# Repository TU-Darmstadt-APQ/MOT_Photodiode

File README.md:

# MOT Photodiode
This is a photodiode board with a transimpedance amplifier for [S-100](https://osioptoelectronics.com/media/pages/products/photodetectors/solderable-chip-photodiodes/s-100vl/1aa00dfa44-1675100439/solderable-chips.pdf) photodiodes used to probe the MOT beams at the QUIPS-C experiment.
The photodiode is inserted into the laser beam on a slide-in unit ([slide_in_mount](photodiode_mount/slide_in_mount.ipt) in combination with the [photo_plate_slide_in](photodiode_mount/photo_plate_slide_in.ipt)) which can be placed behind the MOT Beam Doublett collimators. This assembly is mounted on a flange screwed to the vacuum chamber (viewport_mount assembly designed by Lars Pause). The photodiode board can be screwed on this holder with two polymer screws. 

## Contents
- [Introduction](#introduction)
- [Design files](#design-files)
- [Related repositories](#related-repositories)
- [Versioning](#versioning)
- [License](#license)

## Introduction
The photodiode board features a single-stage amplifier and a voltage regulator to power the op-amp. The power supply required needs to provide +-15 V via a pin header. The bandwidth of the system is about 10 kHz. For details see [here](datasheet/bandwidth.png).

## Design files
### For production
The design files required for the PCB production and assembly can be found on the [releases](../../releases) page and include the following resources:

- Schematics as a PDF
- Gerber files
- Pick & place position files
- Bill of materials as a CSV file and also as an interactive HTML version
- Mechanical design files for manufacturing the housing as PDF

The latest revision of those files can be found [here](../../releases/latest).

### For editing
To work on the [KiCad](https://www.kicad.org/) design files, a number of external libraries are needed. Those libraries show up as empty folders in the zip file, because they are not included in the release, but must be downloaded separately from the links given [below](#related-repositories). This can be avoided by checking out the whole repository using git. This way the libraries will be downloaded as well. Use the following command to clone the git repository along with the submodules  using the `--recurse-submodules` flag.
```
git clone --recurse-submodules https://github.com/TU-Darmstadt-APQ/MOT_Photodiode.git
```

## Related repositories
See the following repositories for more information as these are part of the [design files](#design Files).

- [KiCad footprints](https://github.com/PatrickBaus/footprints.pretty)
- [KiCAD 3D models](https://github.com/PatrickBaus/footprints.3dshapes)
- [KiCAD schematic libraries](https://github.com/PatrickBaus/KiCad-libraries)

## Versioning
I use [SemVer](http://semver.org/) for versioning. For the versions available, see the [tags](../../tags) available for this repository.

- MAJOR versions in this context mean a breaking change to the external interface of the hardware like different connectors or functions.
- MINOR versions contain changes to the hardware that only affect the inner workings of the circuit, but otherwise the performance is unaffected.
- PATCH versions do not affect the schematics or invalidate older bill of materials. These changes may include updated components (to replace obsolete parts for example), an updated silkscreen, or fixed typos.

## License
This work is released under the CERN-OHL-W
See [https://ohwr.org/cern_ohl_w_v2.pdf](https://ohwr.org/cern_ohl_w_v2.pdf) or the included [LICENSE](LICENSE) file for more information.

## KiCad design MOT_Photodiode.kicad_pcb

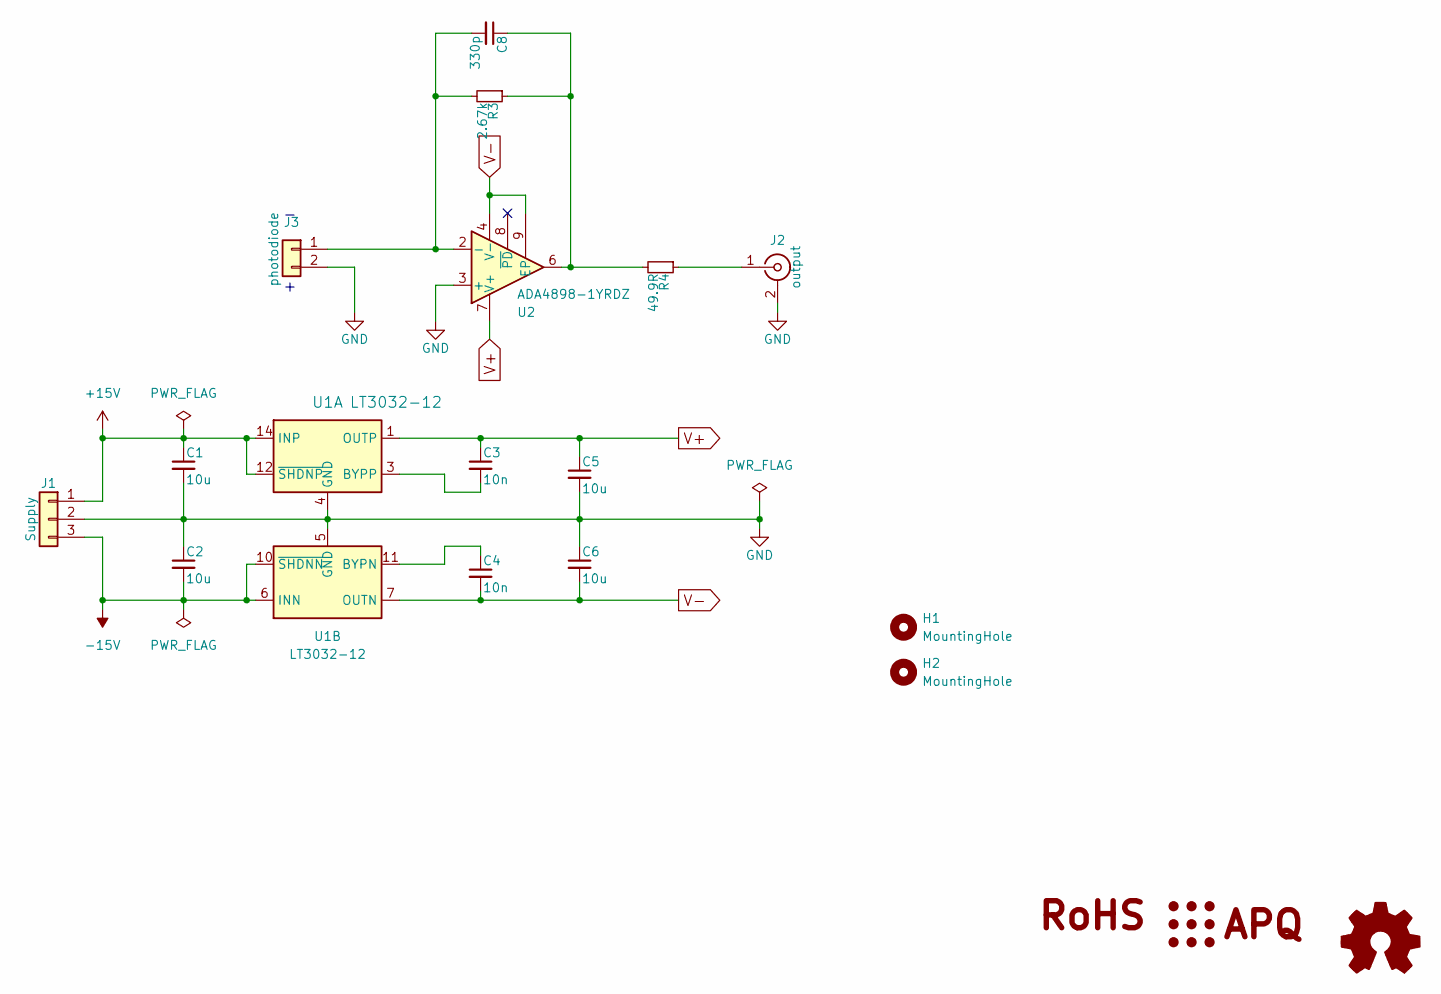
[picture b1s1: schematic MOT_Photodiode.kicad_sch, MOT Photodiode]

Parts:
C1, C2, C5, C6: 10u; C_1210_3225Metric
C3, C4: 10n; C_0603_1608Metric
C8: 330p; C_0603_1608Metric
H1, H2: MountingHole; MountingHole_3.2mm_M3
J1: Supply; PinHeader_1x03_P2.54mm_Vertical
J2: output; SMA_Amphenol_132134_Vertical
J3: photodiode; PinHeader_1x02_P2.54mm_Vertical
R3: 2.67k; R_0603_1608Metric
R4: 49.9R; R_1210_3225Metric
SYM1: Logo_Open_Hardware_Small; OSHW-Logo_7.5x8mm_SilkScreen
SYM2: Logo_APQ; APQ-Logo_small
U1: LT3032-12; Linear_DE14MA
U2: ADA4898-1YRDZ; SOIC-8-1EP_3.9x4.9mm_P1.27mm_EP2.29x3mm

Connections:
+15V: C1.1, J1.1, U1.12 (~SHDNP), U1.14 (INP)
-15V: C2.2, J1.3, U1.6 (INN), U1.9 (INN), U1.10 (~SHDNN)
GND: C1.2, C2.1, C5.2, C6.1, J1.2, J2.2 (Ext), J3.2, U1.4 (GND), U1.5 (GND), U2.3 (+)
unnamed: C8.1, R3.1, R4.2, U2.6
unnamed: J2.1 (In), R4.1
unnamed: C8.2, J3.1, R3.2, U2.2 (-)
unnamed: C3.2, U1.3 (BYPP)
unnamed: C4.1, U1.11 (BYPN)
V+: C3.1, C5.1, U1.1 (OUTP), U2.7 (V+)
V-: C4.2, C6.2, U1.7 (OUTN), U2.4 (V-), U2.9 (EP)

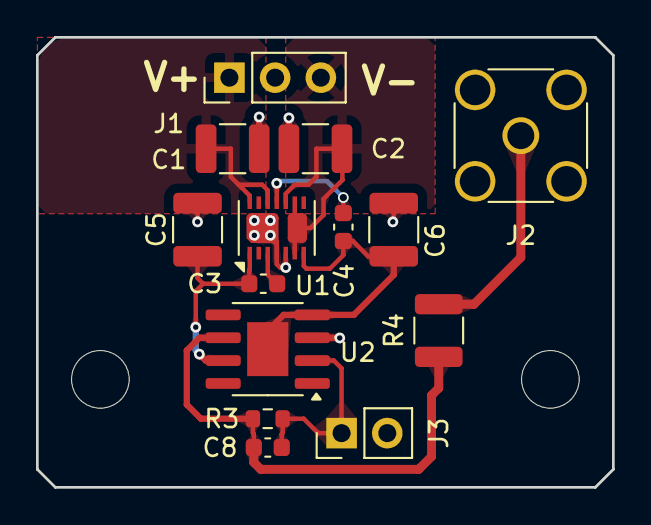
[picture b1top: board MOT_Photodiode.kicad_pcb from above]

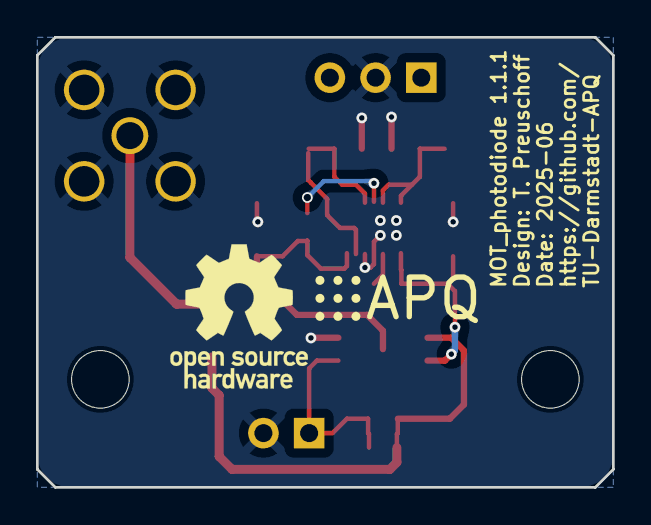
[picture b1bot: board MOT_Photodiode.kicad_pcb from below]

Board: 2 copper layers, 32.0 x 25.0 mm, 18 parts (2 on the bottom side), 10 nets.

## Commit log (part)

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2025-02-27 Cleanup
2025-02-27 Added logos
2025-02-27 Chamfered corners
2025-02-27 Reduced via drill size from 0.4 mm to 0.3 mm
2025-02-27 Added teardrops
2025-02-27 Added BOM
2025-02-27 Added readme
2025-02-27 Added license
2025-02-28 add description
2025-02-28 add comment for to versioning
2025-03-07 add ipt inventor Files
    Original files and whole assembly of viewport_mount can be found on Brain:
    Labortechnik\Mechanik\QUIPS_C\Vakuumkammer_assembly\viewport_flanges
2025-06-24 Update files to KiCad 9
2025-06-24 Bump CI to KiCad 9
2025-06-24 Refilled copper pour
2025-06-24 Bump version to 1.1.1
2025-06-24 More version bumping to 1.1.1
2025-06-24 Update/kicad9 (#2)
    * Update files to KiCad 9 incl. footprint updates
    * Bump CI to KiCad 9
    * Refilled copper pour
    * Bump version to 1.1.1
2025-06-24 Updated readme and added mechanical design files (#1)
    * add description
    * add ipt inventor Files
    Original files and whole assembly of viewport_mount can be found on Brain:
    Labortechnik\Mechanik\QUIPS_C\Vakuumkammer_assembly\viewport_flanges
2025-08-05 [gha] Bump actions/download-artifact from 4 to 5
    Bumps [actions/download-artifact](https://github.com/actions/download-artifact) from 4 to 5.
    - [Release notes](https://github.com/actions/download-artifact/releases)
    - [Commits](https://github.com/actions/download-artifact/compare/v4...v5)
    ---
    updated-dependencies:
    - dependency-name: actions/download-artifact
2025-08-06 [gha] Bump actions/download-artifact from 4 to 5 (#3)
    Bumps [actions/download-artifact](https://github.com/actions/download-artifact) from 4 to 5.
    - [Release notes](https://github.com/actions/download-artifact/releases)
    - [Commits](https://github.com/actions/download-artifact/compare/v4...v5)
    ---
    updated-dependencies:
    - dependency-name: actions/download-artifact
2025-08-12 [gha] Bump actions/checkout from 4 to 5
    Bumps [actions/checkout](https://github.com/actions/checkout) from 4 to 5.
    - [Release notes](https://github.com/actions/checkout/releases)
    - [Changelog](https://github.com/actions/checkout/blob/main/CHANGELOG.md)
    - [Commits](https://github.com/actions/checkout/compare/v4...v5)
    ---
    updated-dependencies:
2025-08-12 [gha] Bump actions/checkout from 4 to 5 (#4)
    Bumps [actions/checkout](https://github.com/actions/checkout) from 4 to 5.
    - [Release notes](https://github.com/actions/checkout/releases)
    - [Changelog](https://github.com/actions/checkout/blob/main/CHANGELOG.md)
    - [Commits](https://github.com/actions/checkout/compare/v4...v5)
    ---
    updated-dependencies:
2025-10-24 [gha] Bump actions/upload-artifact from 4 to 5
    Bumps [actions/upload-artifact](https://github.com/actions/upload-artifact) from 4 to 5.
    - [Release notes](https://github.com/actions/upload-artifact/releases)
    - [Commits](https://github.com/actions/upload-artifact/compare/v4...v5)
    ---
    updated-dependencies:
    - dependency-name: actions/upload-artifact
2025-10-24 [gha] Bump actions/download-artifact from 5 to 6
    Bumps [actions/download-artifact](https://github.com/actions/download-artifact) from 5 to 6.
    - [Release notes](https://github.com/actions/download-artifact/releases)
    - [Commits](https://github.com/actions/download-artifact/compare/v5...v6)
    ---
    updated-dependencies:
    - dependency-name: actions/download-artifact
2025-10-24 [gha] Bump actions/upload-artifact from 4 to 5 (#5)
    Bumps [actions/upload-artifact](https://github.com/actions/upload-artifact) from 4 to 5.
    - [Release notes](https://github.com/actions/upload-artifact/releases)
    - [Commits](https://github.com/actions/upload-artifact/compare/v4...v5)
    ---
    updated-dependencies:
    - dependency-name: actions/upload-artifact
2025-10-24 [gha] Bump actions/download-artifact from 5 to 6 (#6)
    Bumps [actions/download-artifact](https://github.com/actions/download-artifact) from 5 to 6.
    - [Release notes](https://github.com/actions/download-artifact/releases)
    - [Commits](https://github.com/actions/download-artifact/compare/v5...v6)
    ---
    updated-dependencies:
    - dependency-name: actions/download-artifact
2025-11-20 [gha] Bump actions/checkout from 5 to 6
    Bumps [actions/checkout](https://github.com/actions/checkout) from 5 to 6.
    - [Release notes](https://github.com/actions/checkout/releases)
    - [Changelog](https://github.com/actions/checkout/blob/main/CHANGELOG.md)
    - [Commits](https://github.com/actions/checkout/compare/v5...v6)
    ---
    updated-dependencies:
2025-11-20 [gha] Bump actions/checkout from 5 to 6 (#7)
    Bumps [actions/checkout](https://github.com/actions/checkout) from 5 to 6.
    - [Release notes](https://github.com/actions/checkout/releases)
    - [Changelog](https://github.com/actions/checkout/blob/main/CHANGELOG.md)
    - [Commits](https://github.com/actions/checkout/compare/v5...v6)
    ---
    updated-dependencies:
2025-11-25 Bump libraries from `80d58ef` to `ba5563d`
    Bumps [libraries](https://github.com/PatrickBaus/KiCad-libraries) from `80d58ef` to `ba5563d`.
    - [Commits](https://github.com/PatrickBaus/KiCad-libraries/compare/80d58efa29fc28aa49b090516bd5b7168ac740c8...ba5563d66c23dea06d561adcb039ddac5a03efdf)
    ---
    updated-dependencies:
    - dependency-name: libraries
    dependency-version: ba5563d66c23dea06d561adcb039ddac5a03efdf
2025-11-25 Bump libraries from `80d58ef` to `ba5563d` (#8)
    Bumps [libraries](https://github.com/PatrickBaus/KiCad-libraries) from `80d58ef` to `ba5563d`.
    - [Commits](https://github.com/PatrickBaus/KiCad-libraries/compare/80d58efa29fc28aa49b090516bd5b7168ac740c8...ba5563d66c23dea06d561adcb039ddac5a03efdf)
    ---
    updated-dependencies:
    - dependency-name: libraries
    dependency-version: ba5563d66c23dea06d561adcb039ddac5a03efdf
2025-12-12 [gha] Bump actions/upload-artifact from 5 to 6
    Bumps [actions/upload-artifact](https://github.com/actions/upload-artifact) from 5 to 6.
    - [Release notes](https://github.com/actions/upload-artifact/releases)
    - [Commits](https://github.com/actions/upload-artifact/compare/v5...v6)
    ---
    updated-dependencies:
    - dependency-name: actions/upload-artifact
2025-12-12 [gha] Bump actions/download-artifact from 6 to 7
    Bumps [actions/download-artifact](https://github.com/actions/download-artifact) from 6 to 7.
    - [Release notes](https://github.com/actions/download-artifact/releases)
    - [Commits](https://github.com/actions/download-artifact/compare/v6...v7)
    ---
    updated-dependencies:
    - dependency-name: actions/download-artifact
2025-12-13 [gha] Bump actions/upload-artifact from 5 to 6 (#9)
    Bumps [actions/upload-artifact](https://github.com/actions/upload-artifact) from 5 to 6.
    - [Release notes](https://github.com/actions/upload-artifact/releases)
    - [Commits](https://github.com/actions/upload-artifact/compare/v5...v6)
    ---
    updated-dependencies:
    - dependency-name: actions/upload-artifact
2025-12-13 [gha] Bump actions/download-artifact from 6 to 7 (#10)
    Bumps [actions/download-artifact](https://github.com/actions/download-artifact) from 6 to 7.
    - [Release notes](https://github.com/actions/download-artifact/releases)
    - [Commits](https://github.com/actions/download-artifact/compare/v6...v7)
    ---
    updated-dependencies:
    - dependency-name: actions/download-artifact
2025-12-16 Bump libraries from `ba5563d` to `d79317d`
    Bumps [libraries](https://github.com/PatrickBaus/KiCad-libraries) from `ba5563d` to `d79317d`.
    - [Commits](https://github.com/PatrickBaus/KiCad-libraries/compare/ba5563d66c23dea06d561adcb039ddac5a03efdf...d79317d926704a58090a36fac06bfafa731a048b)
    ---
    updated-dependencies:
    - dependency-name: libraries
    dependency-version: d79317d926704a58090a36fac06bfafa731a048b
2025-12-16 Bump libraries from `ba5563d` to `d79317d` (#11)
    Bumps [libraries](https://github.com/PatrickBaus/KiCad-libraries) from `ba5563d` to `d79317d`.
    - [Commits](https://github.com/PatrickBaus/KiCad-libraries/compare/ba5563d66c23dea06d561adcb039ddac5a03efdf...d79317d926704a58090a36fac06bfafa731a048b)
    ---
    updated-dependencies:
    - dependency-name: libraries
    dependency-version: d79317d926704a58090a36fac06bfafa731a048b
2026-02-06 Bump libraries from `d79317d` to `4179135`
    Bumps [libraries](https://github.com/PatrickBaus/KiCad-libraries) from `d79317d` to `4179135`.
    - [Commits](https://github.com/PatrickBaus/KiCad-libraries/compare/d79317d926704a58090a36fac06bfafa731a048b...41791358010d2de5d2401e25bd30de257630acf6)
    ---
    updated-dependencies:
    - dependency-name: libraries
    dependency-version: 41791358010d2de5d2401e25bd30de257630acf6
2026-02-07 Bump libraries from `d79317d` to `4179135` (#12)
    Bumps [libraries](https://github.com/PatrickBaus/KiCad-libraries) from `d79317d` to `4179135`.
    - [Commits](https://github.com/PatrickBaus/KiCad-libraries/compare/d79317d926704a58090a36fac06bfafa731a048b...41791358010d2de5d2401e25bd30de257630acf6)
    ---
    updated-dependencies:
    - dependency-name: libraries
    dependency-version: 41791358010d2de5d2401e25bd30de257630acf6
2026-02-26 [gha] Bump actions/upload-artifact from 6 to 7
    Bumps [actions/upload-artifact](https://github.com/actions/upload-artifact) from 6 to 7.
    - [Release notes](https://github.com/actions/upload-artifact/releases)
    - [Commits](https://github.com/actions/upload-artifact/compare/v6...v7)
    ---
    updated-dependencies:
    - dependency-name: actions/upload-artifact
2026-02-26 [gha] Bump actions/download-artifact from 7 to 8
    Bumps [actions/download-artifact](https://github.com/actions/download-artifact) from 7 to 8.
    - [Release notes](https://github.com/actions/download-artifact/releases)
    - [Commits](https://github.com/actions/download-artifact/compare/v7...v8)
    ---
    updated-dependencies:
    - dependency-name: actions/download-artifact
2026-02-27 [gha] Bump actions/upload-artifact from 6 to 7 (#13)
    Bumps [actions/upload-artifact](https://github.com/actions/upload-artifact) from 6 to 7.
    - [Release notes](https://github.com/actions/upload-artifact/releases)
    - [Commits](https://github.com/actions/upload-artifact/compare/v6...v7)
    ---
    updated-dependencies:
    - dependency-name: actions/upload-artifact
2026-02-27 [gha] Bump actions/download-artifact from 7 to 8 (#14)
    Bumps [actions/download-artifact](https://github.com/actions/download-artifact) from 7 to 8.
    - [Release notes](https://github.com/actions/download-artifact/releases)
    - [Commits](https://github.com/actions/download-artifact/compare/v7...v8)
    ---
    updated-dependencies:
    - dependency-name: actions/download-artifact
2026-06-18 [gha] Bump actions/checkout from 6 to 7
    Bumps [actions/checkout](https://github.com/actions/checkout) from 6 to 7.
    - [Release notes](https://github.com/actions/checkout/releases)
    - [Changelog](https://github.com/actions/checkout/blob/main/CHANGELOG.md)
    - [Commits](https://github.com/actions/checkout/compare/v6...v7)
    ---
    updated-dependencies:
2026-06-19 [gha] Bump actions/checkout from 6 to 7 (#15)
    Bumps [actions/checkout](https://github.com/actions/checkout) from 6 to 7.
    - [Release notes](https://github.com/actions/checkout/releases)
    - [Changelog](https://github.com/actions/checkout/blob/main/CHANGELOG.md)
    - [Commits](https://github.com/actions/checkout/compare/v6...v7)
    ---
    updated-dependencies:

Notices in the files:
MOT_Photodiode.kicad_pcb:
Copyright (©) 2025, Patrick Baus
Licensed under CERN OHL v.1.2
README.md:
License: CERN-OHL-W-2.0
